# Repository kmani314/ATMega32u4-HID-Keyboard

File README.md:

## ATMega32u4 HID Keyboard
###### Board Project 2019 - Krishna Mani
This is software for ATMega32u4 or compatible AVR hardware USB chips that implements a standard-complying HID keyboard using only AVR-LIBC.

I used these for reference when coding:

1. https://www.avrfreaks.net/forum/usb-initialization-problem
2. https://www.pjrc.com/teensy/usb_keyboard.html
3. https://www.usb.org/sites/default/files/documents/hid1_11.pdf
4. https://www.avrfreaks.net/forum/help-properly-initializing-usb-hardware-atmega32u4
5. https://www.beyondlogic.org/usbnutshell/usb1.shtml
6. http://ww1.microchip.com/downloads/en/devicedoc/atmel-7766-8-bit-avr-atmega16u4-32u4_datasheet.pdf
7. https://github.com/arduino/ArduinoCore-avr/blob/master/cores/arduino/USBCore.cpp
8. http://sdphca.ucsd.edu/lab_equip_manuals/usb_20.pdf

Finished Board:

### Hardware

##### Microcontroller
The ATMega32u4 controls the scanning matrix and the USB interface. I chose it because of its hardware USB interface and because it has enough I/O pins to support the whole keyboard without needing any multiplexing. It also has enough flash and SRAM for storing layouts. The 32u4 on the keyboard runs at 16mHz from an external crystal oscillator with 22pF load capacitors. It is powered directly from the USB lines with filtering capacitors.
##### PCBs
Initially, I needed to test the main microcontroller circuit of the keyboard to ensure that it worked and that the USB worked, because I had developed on an Arduino Leonardo. (boards/ATMegaTestingBoard.brd)

##### ATMega32u4 Circuit
The portion of the board for the ATMega32u4 is fairly standard for this chip and is similar to the Arduino Leonardo, excluding the power regulators. It consists of the chip, the oscillator and load caps, the power and layer leds, the reset switch, the USB connector and data resistors, the ICSP pins, and the filtering caps on the underside of the board.

Top / Bottom (boards/Keyboard.brd):

The rest of the board is the scanning matrix. The rows and columns use up the majority of the I/O on the chip.
The matrix is standard for a keyboard - one pin of each switch in a column is connected through a diode to every other one in the column. Then, the remaining pin in each switch is common with the row. I used through hole diodes because they are much easier to solder. The switches are standard mechanical keyboard switches, and the footprints are from here: https://github.com/mknyszek/gateron-eagle
To read the matrix, the row pins are pulled high through internal pull-up resistors. One column at a time is set low, so that a pressed key would pull the row pin low, signaling a key press at the current row and column index.

Top / Bottom matrix (boards/Keyboard.brd):

##### Board Assembly
Assembling the board was straightforward except for the SMD components, specifically the TQFP ATMega32u4. It is really easy to bridge several pads very quickly, and completely ruin the chip. I soldered these by holding them in place and tacking down the corners so the chip didn’t move. I used a lot of flux, then with very little solder dragged the iron across the pins. The USB connector is also really difficult, I soldered the anchor pins and then the pins. It is really easy to bridge the pins with the ground enclosure. Using super glue after ensures that the connector doesn’t snap off when you unplug the cable.

### Code
##### USB
First, the USB controller of the 32u4 is initialized. This is handled in the function `usb_init()`. The PLL (Phase Locked Loop) is initialized, taking the external clock as input. It runs at 48mHz and acts as the USB clock. After the USB controller is initialized, the control endpoint is set up and will receive setup packets from the host. The setup packets, handled in the ISR `USB_gen_vect`, elicit responses from the keyboard based on the values of bmRequestType and bRequest, which determine the type of request. After the host has requested and received the USB descriptors, and the keyboard has correctly responded to HID-specific requests, the host can enumerate the device and use it as an input device.

The key repeat feature of modern keyboards is handled separately from the standard functions `usb_send()` and `usb_send_keypress()`. If a key is held down for some period of time, it should be repeated until it is released. This is taken care of in the ISR `USB_gen_vect`, specifically when the SOFE (start of frame) bit is set. This interrupt triggers at 1kHz, which is how often the host sends start of frame packets. If no keypresses have been generated since the period time, which is kept track of with keyboard_idle_value and current_idle, the entire HID report is resent to facilitate key repeat. The period of time the device should wait before resending the report is set from the wValue in the HID request SET_IDLE.
##### Matrix Software
The scanning matrix of the keyboard uses the current sourcing and internal pullups of the I/O ports on the 32u4. Because of the orientation of the diodes, the columns of the keyboard are set low when they are going to be read. The rows are always pulled up, meaning that if a key is pressed, it will be pulled low because the switch is connecting the row and columns. The matrix scanning is repeated quickly, and changes in key state are recorded in the six-byte USB HID report. The report is six bytes to support six concurrent key presses. The keyboard dynamically assigns and removes keys from the report to support 6-key-rollover, and it also resets the reports on layout layer shifts to prevent strange glitches. The meta and special keys like CTRL, ALT, and SHIFT have their own byte apart from the report, where each bit represents a different key. This is according to the USB HID Spec.

The rows and columns of the recorded keypresses are translated into actual keycodes from the specified layout in `layout.h`. The layout is written from the standard HID keycodes in `keys.h`. Because the keyboard does not have enough physical keys to support all the letters, function, and number keys, some keys are macros that change the mappings of all the keys. These keys are handled separately and do not generate keypress events on their own. Rather, they update the current layer that the scanning matrix is reporting keypresses from to change the keycodes.
### Improvements
1. Changing the routing on PORTD to make it iterable, making the code more readable and cleaner.
2. Using USB-C instead of micro b, meaning that you would not need a dongle for use with newer macs. This would, however, make it much more difficult to solder and the PCB more complicated, since the USB-C connectors have 24 pins.
3. Using the BGA package for the ATMega32u4 so that it could fit in between switches on the underside of the board, meaning that the PCB would only have to be as big as to fit the switches. This would make it more compact.
4. Using symmetrical keycaps so that the keycaps aren’t skewed when using keyboard layouts other than QWERTY.
5. Adding support for a dedicated FN key endpoint and Caps lock and num lock; currently you have to remap function to media keys with a third party tool for the media keys on the keyboard to work on touch bar macs.
6. Move the ICSP connector down, right now you have to bend the power LED up for the connector to make contact with the headers.
7. Route the third layer led to a different I/O port, right now only two of the three LEDs work.

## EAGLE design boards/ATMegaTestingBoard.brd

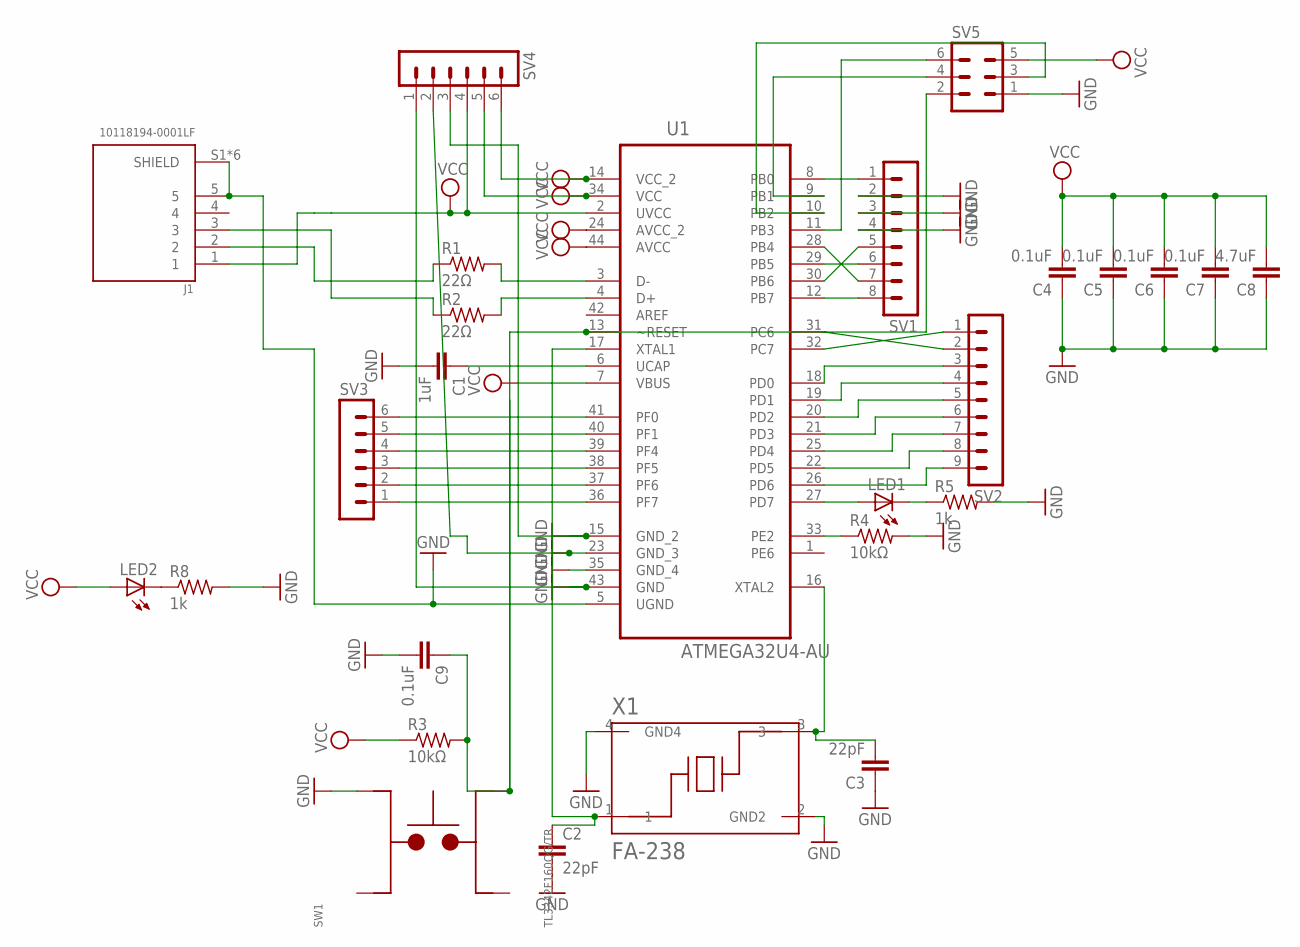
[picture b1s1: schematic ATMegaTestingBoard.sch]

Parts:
C1: 1uF; C0805
C2, C3: 22pF; C0805
C4, C5, C6, C7, C9: 0.1uF; C0805
C8: 4.7uF; C0805
J1: 10118194-0001LF; AMPHENOL_10118194-0001LF
LED1, LED2: LEDCHIPLED_0805; CHIPLED_0805
R1, R2: 22Ω; R0805
R3, R4: 10kΩ; R0805
R5, R8: 1k; R0805
SV1: MA08-1
SV2: MA09-1
SV3, SV4: MA06-1
SV5: MA03-2
SW1: TL3342F160QG/TR; SW_TL3342F160QG/TR
U1: ATMEGA32U4-AU; QFP80P1200X1200X120-44N
X1: FA-238; OSCCC320X250X70-4N

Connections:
GND: C1.2, C2.2, C3.1, C4.1, C5.1, C6.1, C7.1, C8.1, C9.2, J1.5, J1.S1 (SHIELD), J1.S2 (SHIELD), J1.S3 (SHIELD), J1.S4 (SHIELD), J1.S5 (SHIELD), J1.S6 (SHIELD), R4.2, R5.2, R8.2, SV1.2, SV1.3, SV1.4, SV4.1, SV4.2, SV4.3, SV5.1, SW1.4, U1.5 (UGND), U1.15 (GND_2), U1.23 (GND_3), U1.35 (GND_4), U1.43 (GND), X1.2 (GND2), X1.4 (GND4)
unnamed: R1.2, U1.3 (D-)
unnamed: J1.3, R2.1
unnamed: J1.2, R1.1
unnamed: C1.1, U1.6 (UCAP)
unnamed: R2.2, U1.4 (D+)
unnamed: SV1.1, U1.8 (PB0)
unnamed: C9.1, R3.2, SV5.2, SW1.2, U1.13 (~RESET)
unnamed: C2.1, U1.17 (XTAL1), X1.1
unnamed: R4.1, U1.33 (PE2)
unnamed: C3.2, U1.16 (XTAL2), X1.3
unnamed: LED1.A, U1.27 (PD7)
unnamed: LED1.C, R5.1
unnamed: SV1.7, U1.28 (PB4)
unnamed: SV1.5, U1.30 (PB6)
unnamed: LED2.C, R8.1
unnamed: SV5.6, U1.11 (PB3)
unnamed: SV5.4, U1.9 (PB1)
unnamed: SV5.3, U1.10 (PB2)
unnamed: SV1.6, U1.29 (PB5)
unnamed: SV2.2, U1.31 (PC6)
unnamed: SV2.1, U1.32 (PC7)
unnamed: SV1.8, U1.12 (PB7)
unnamed: SV2.3, U1.18 (PD0)
unnamed: SV2.4, U1.19 (PD1)
unnamed: SV2.5, U1.20 (PD2)
unnamed: SV2.6, U1.21 (PD3)
unnamed: SV2.7, U1.25 (PD4)
unnamed: SV2.8, U1.22 (PD5)
unnamed: SV2.9, U1.26 (PD6)
unnamed: SV3.6, U1.41 (PF0)
unnamed: SV3.5, U1.40 (PF1)
unnamed: SV3.4, U1.39 (PF4)
unnamed: SV3.3, U1.38 (PF5)
unnamed: SV3.2, U1.37 (PF6)
unnamed: SV3.1, U1.36 (PF7)
VCC: C4.2, C5.2, C6.2, C7.2, C8.2, J1.1, LED2.A, R3.1, SV4.4, SV4.5, SV4.6, SV5.5, U1.2 (UVCC), U1.7 (VBUS), U1.14 (VCC_2), U1.24 (AVCC_2), U1.34 (VCC), U1.44 (AVCC)

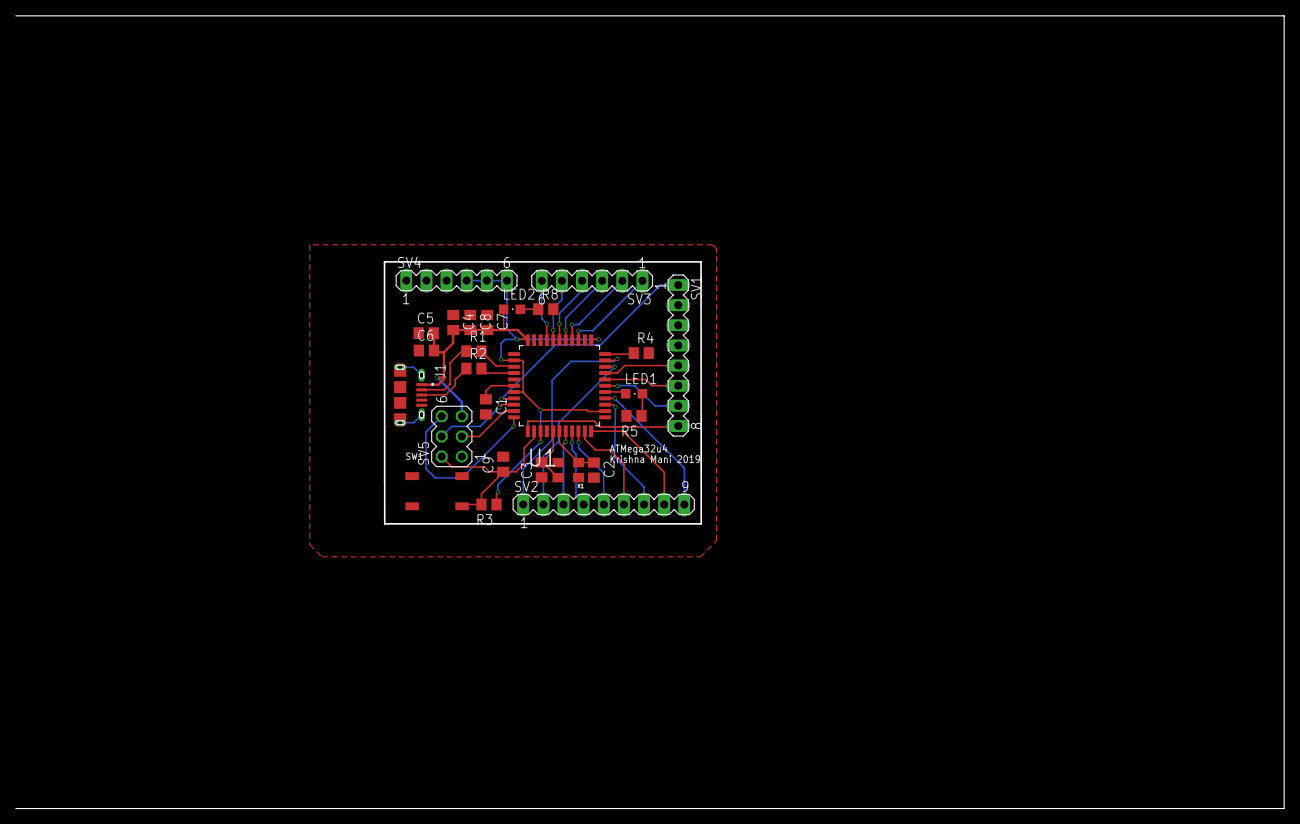
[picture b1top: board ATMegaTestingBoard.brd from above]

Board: 2 copper layers, 160.0 x 100.0 mm, 26 parts (0 on the bottom side), 37 nets.

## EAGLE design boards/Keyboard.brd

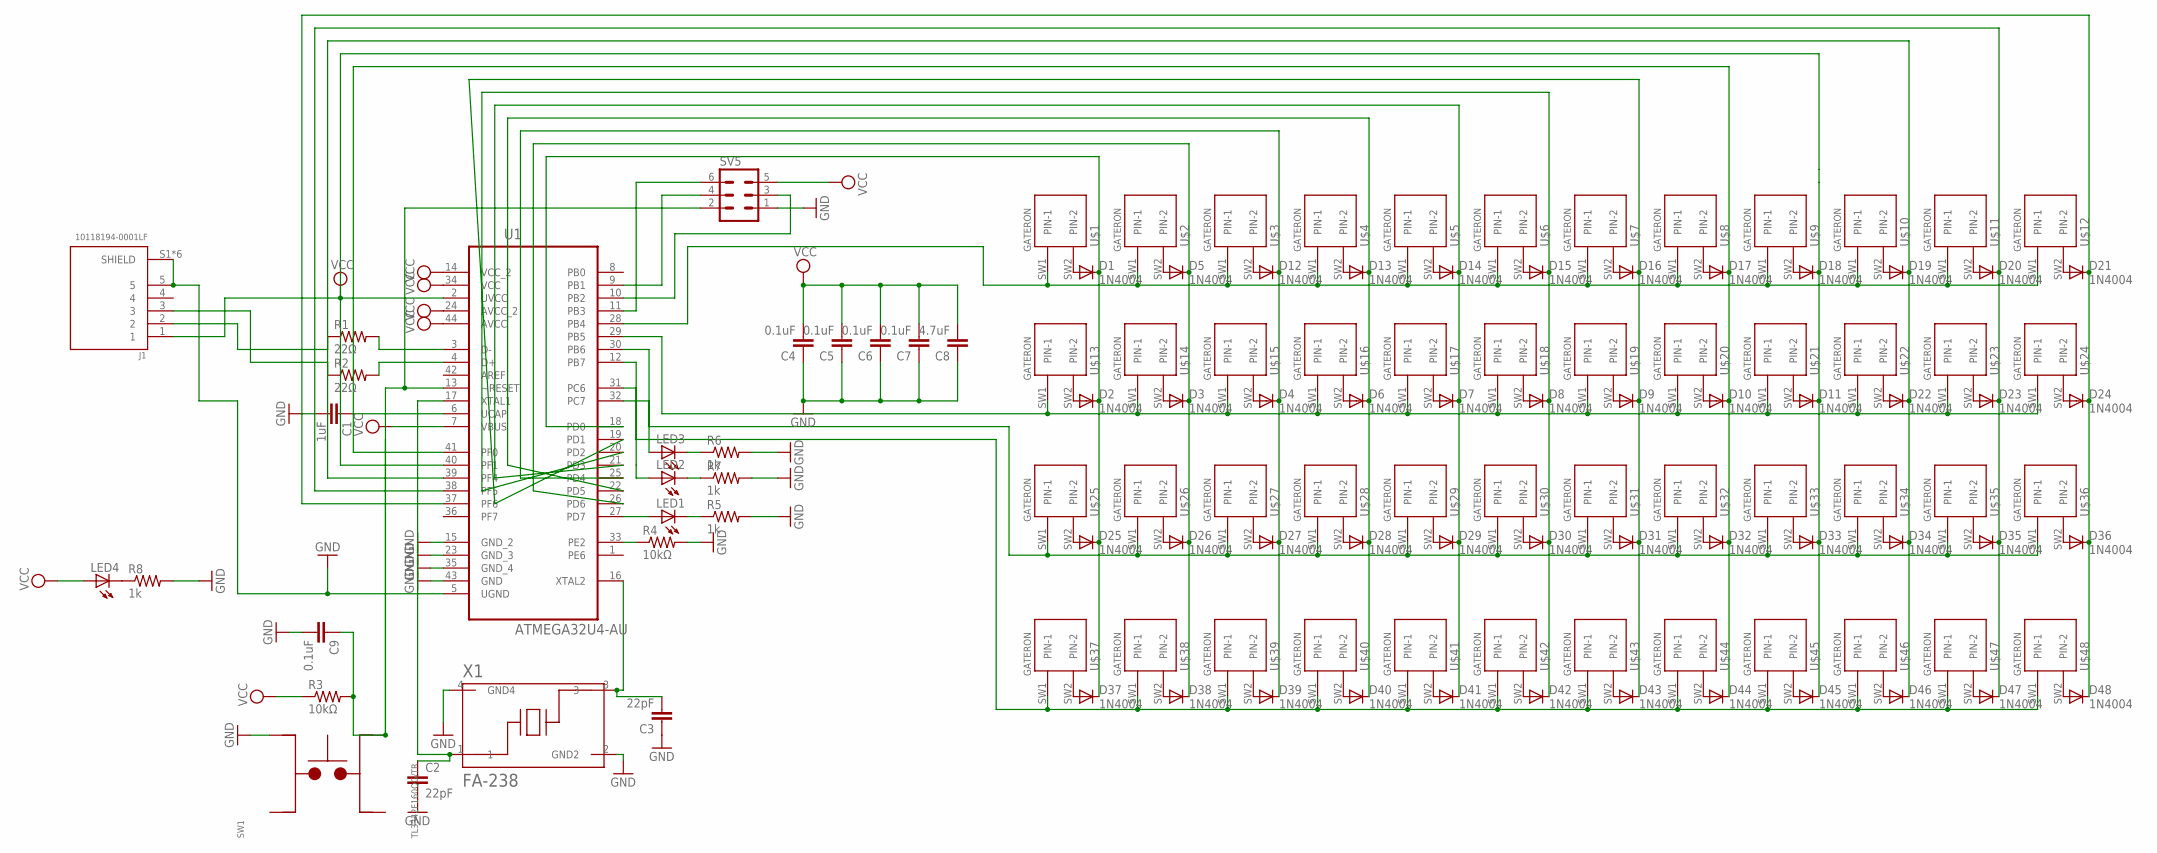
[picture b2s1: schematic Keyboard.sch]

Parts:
C1: 1uF; C0805
C2, C3: 22pF; C0805
C4, C5, C6, C7, C9: 0.1uF; C0805
C8: 4.7uF; C0805
D1, D2, D3, D4, D5, D6, D7, D8, D9, D10, D11, D12, D13, D14, D15, D16, D17, D18, D19, D20, D21, D22, D23, D24, D25, D26, D27, D28, D29, D30, D31, D32, D33, D34, D35, D36, D37, D38, D39, D40, D41, D42, D43, D44, D45, D46, D47, D48: 1N4004; DO41-10
J1: 10118194-0001LF; AMPHENOL_10118194-0001LF
LED1, LED2, LED3, LED4: LED_ELD260; LED_LD260
R1, R2: 22Ω; R0805
R3, R4: 10kΩ; R0805
R5, R6, R7, R8: 1k; R0805
SV5: MA03-2
SW1: TL3342F160QG/TR; SW_TL3342F160QG/TR
U1: ATMEGA32U4-AU; QFP80P1200X1200X120-44N
U$1, U$2, U$3, U$4, U$5, U$6, U$7, U$8, U$9, U$10, U$11, U$12, U$13, U$14, U$15, U$16, U$17, U$18, U$19, U$20, U$21, U$22, U$23, U$24, U$25, U$26, U$27, U$28, U$29, U$30, U$31, U$32, U$33, U$34, U$35, U$36, U$37, U$38, U$39, U$40, U$41, U$42, U$43, U$44, U$45, U$46, U$47, U$48: GATERON
X1: FA-238; OSCCC320X250X70-4N

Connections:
GND: C1.2, C2.2, C3.1, C4.1, C5.1, C6.1, C7.1, C8.1, C9.2, J1.5, J1.S1 (SHIELD), J1.S2 (SHIELD), J1.S3 (SHIELD), J1.S4 (SHIELD), J1.S5 (SHIELD), J1.S6 (SHIELD), R4.2, R5.2, R6.2, R7.2, R8.2, SV5.1, SW1.4, U1.5 (UGND), U1.15 (GND_2), U1.23 (GND_3), U1.35 (GND_4), U1.43 (GND), X1.2 (GND2), X1.4 (GND4)
unnamed: R1.2, U1.3 (D-)
unnamed: J1.3, R2.1
unnamed: J1.2, R1.1
unnamed: C1.1, U1.6 (UCAP)
unnamed: R2.2, U1.4 (D+)
unnamed: U1.28 (PB4), U$1.SW1 (PIN-1), U$2.SW1 (PIN-1), U$3.SW1 (PIN-1), U$4.SW1 (PIN-1), U$5.SW1 (PIN-1), U$6.SW1 (PIN-1), U$7.SW1 (PIN-1), U$8.SW1 (PIN-1), U$9.SW1 (PIN-1), U$10.SW1 (PIN-1), U$11.SW1 (PIN-1), U$12.SW1 (PIN-1)
unnamed: C9.1, R3.2, SV5.2, SW1.2, U1.13 (~RESET)
unnamed: C2.1, U1.17 (XTAL1), X1.1
unnamed: R4.1, U1.33 (PE2)
unnamed: C3.2, U1.16 (XTAL2), X1.3
unnamed: LED1.A, U1.27 (PD7)
unnamed: LED1.K (C), R5.1
unnamed: U1.29 (PB5), U$13.SW1 (PIN-1), U$14.SW1 (PIN-1), U$15.SW1 (PIN-1), U$16.SW1 (PIN-1), U$17.SW1 (PIN-1), U$18.SW1 (PIN-1), U$19.SW1 (PIN-1), U$20.SW1 (PIN-1), U$21.SW1 (PIN-1), U$22.SW1 (PIN-1), U$23.SW1 (PIN-1), U$24.SW1 (PIN-1)
unnamed: D2.A, U$13.SW2 (PIN-2)
unnamed: LED4.K (C), R8.1
unnamed: SV5.6, U1.11 (PB3)
unnamed: SV5.4, U1.9 (PB1)
unnamed: SV5.3, U1.10 (PB2)
unnamed: D3.A, U$14.SW2 (PIN-2)
unnamed: D1.A, U$1.SW2 (PIN-2)
unnamed: D4.A, U$15.SW2 (PIN-2)
unnamed: D6.A, U$16.SW2 (PIN-2)
unnamed: D7.A, U$17.SW2 (PIN-2)
unnamed: D5.A, U$2.SW2 (PIN-2)
unnamed: D8.A, U$18.SW2 (PIN-2)
unnamed: D9.A, U$19.SW2 (PIN-2)
unnamed: D10.A, U$20.SW2 (PIN-2)
unnamed: D11.A, U$21.SW2 (PIN-2)
unnamed: D22.A, U$22.SW2 (PIN-2)
unnamed: D23.A, U$23.SW2 (PIN-2)
unnamed: D12.A, U$3.SW2 (PIN-2)
unnamed: D13.A, U$4.SW2 (PIN-2)
unnamed: D14.A, U$5.SW2 (PIN-2)
unnamed: D15.A, U$6.SW2 (PIN-2)
unnamed: D16.A, U$7.SW2 (PIN-2)
unnamed: D17.A, U$8.SW2 (PIN-2)
unnamed: D18.A, U$9.SW2 (PIN-2)
unnamed: D19.A, U$10.SW2 (PIN-2)
unnamed: D20.A, U$11.SW2 (PIN-2)
unnamed: D21.A, U$12.SW2 (PIN-2)
unnamed: D24.A, U$24.SW2 (PIN-2)
unnamed: U1.30 (PB6), U$25.SW1 (PIN-1), U$26.SW1 (PIN-1), U$27.SW1 (PIN-1), U$28.SW1 (PIN-1), U$29.SW1 (PIN-1), U$30.SW1 (PIN-1), U$31.SW1 (PIN-1), U$32.SW1 (PIN-1), U$33.SW1 (PIN-1), U$34.SW1 (PIN-1), U$35.SW1 (PIN-1), U$36.SW1 (PIN-1)
unnamed: D25.A, U$25.SW2 (PIN-2)
unnamed: D26.A, U$26.SW2 (PIN-2)
unnamed: D27.A, U$27.SW2 (PIN-2)
unnamed: D28.A, U$28.SW2 (PIN-2)
unnamed: D29.A, U$29.SW2 (PIN-2)
unnamed: D30.A, U$30.SW2 (PIN-2)
unnamed: D31.A, U$31.SW2 (PIN-2)
unnamed: D32.A, U$32.SW2 (PIN-2)
unnamed: D33.A, U$33.SW2 (PIN-2)
unnamed: D34.A, U$34.SW2 (PIN-2)
unnamed: D35.A, U$35.SW2 (PIN-2)
unnamed: D36.A, U$36.SW2 (PIN-2)
unnamed: U1.12 (PB7), U$37.SW1 (PIN-1), U$38.SW1 (PIN-1), U$39.SW1 (PIN-1), U$40.SW1 (PIN-1), U$41.SW1 (PIN-1), U$42.SW1 (PIN-1), U$43.SW1 (PIN-1), U$44.SW1 (PIN-1), U$45.SW1 (PIN-1), U$46.SW1 (PIN-1), U$47.SW1 (PIN-1), U$48.SW1 (PIN-1)
unnamed: D37.A, U$37.SW2 (PIN-2)
unnamed: D38.A, U$38.SW2 (PIN-2)
unnamed: D39.A, U$39.SW2 (PIN-2)
unnamed: D40.A, U$40.SW2 (PIN-2)
unnamed: D41.A, U$41.SW2 (PIN-2)
unnamed: D42.A, U$42.SW2 (PIN-2)
unnamed: D43.A, U$43.SW2 (PIN-2)
unnamed: D44.A, U$44.SW2 (PIN-2)
unnamed: D45.A, U$45.SW2 (PIN-2)
unnamed: D46.A, U$46.SW2 (PIN-2)
unnamed: D47.A, U$47.SW2 (PIN-2)
unnamed: D48.A, U$48.SW2 (PIN-2)
unnamed: D1.C, D2.C, D25.C, D37.C, U1.18 (PD0)
unnamed: D3.C, D5.C, D26.C, D38.C, U1.26 (PD6)
unnamed: D4.C, D12.C, D27.C, D39.C, U1.25 (PD4)
unnamed: D6.C, D13.C, D28.C, D40.C, U1.22 (PD5)
unnamed: D7.C, D14.C, D29.C, D41.C, U1.21 (PD3)
unnamed: D8.C, D15.C, D30.C, D42.C, U1.20 (PD2)
unnamed: D9.C, D16.C, D31.C, D43.C, U1.19 (PD1)
unnamed: D10.C, D17.C, D32.C, D44.C, U1.41 (PF0)
unnamed: D11.C, D18.C, D33.C, D45.C, U1.40 (PF1)
unnamed: D19.C, D22.C, D34.C, D46.C, U1.39 (PF4)
unnamed: D20.C, D23.C, D35.C, D47.C, U1.38 (PF5)
unnamed: D21.C, D24.C, D36.C, D48.C, U1.37 (PF6)
unnamed: LED3.K (C), R6.1
unnamed: LED2.K (C), R7.1
unnamed: LED2.A, U1.31 (PC6)
unnamed: LED3.A, U1.32 (PC7)
VCC: C4.2, C5.2, C6.2, C7.2, C8.2, J1.1, LED4.A, R3.1, SV5.5, U1.2 (UVCC), U1.7 (VBUS), U1.14 (VCC_2), U1.24 (AVCC_2), U1.34 (VCC), U1.44 (AVCC)

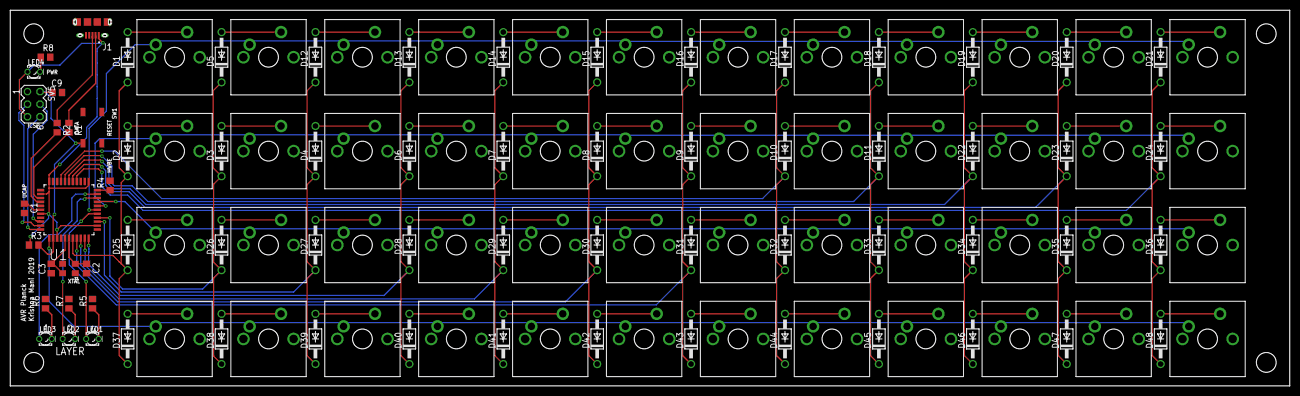
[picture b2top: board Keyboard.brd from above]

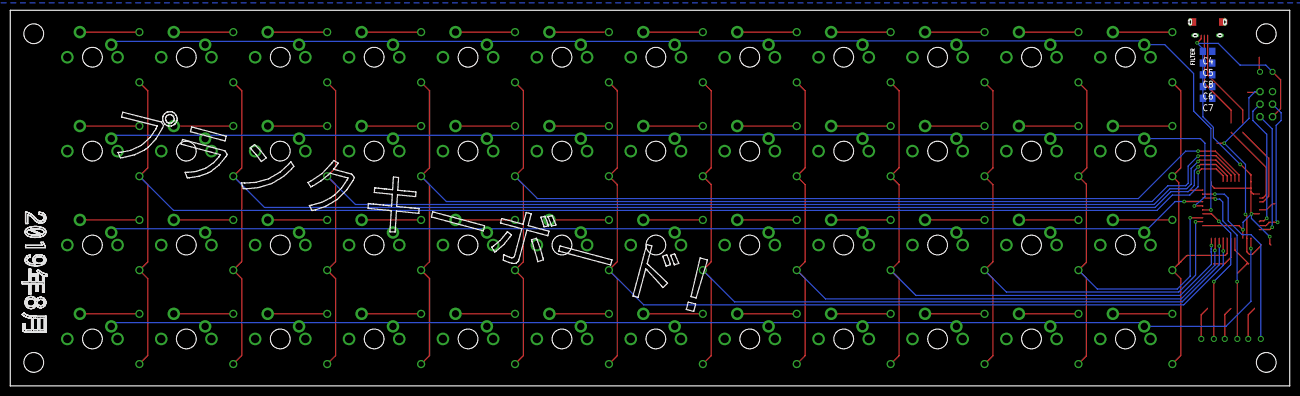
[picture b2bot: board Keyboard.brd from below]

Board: 2 copper layers, 258.9 x 76.0 mm, 122 parts (5 on the bottom side), 85 nets.

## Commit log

2019-07-15 Add basic readme
2019-07-16 Basic CMake, usb_init
2019-07-17 Recongnizes EORSTE now
2019-07-18 Not really working
2019-07-18 Works, receiving RXSTPI, problem was bad PLL setup
2019-07-19 Add README references, usb_config_status bool
2019-07-19 README
2019-07-19 github markdown is strange
2019-07-19 almost fixed readme
2019-07-19 add ul to readme
2019-07-19 alright, finally add ul
2019-07-19 Update README for first part of writeup
2019-07-19 Add README table
2019-07-19 fix table
2019-07-19 final table
2019-07-21 Started on setup packets and descriptors
2019-07-22 Working on descriptors
2019-07-23 Write HID descriptor
2019-07-23 Finish Descriptors
2019-07-24 address setup done, receives GET_DESCRIPTOR
2019-07-26 Add working device enumeration
2019-07-26 working enumeration with 32 byte endpoint properly setup
2019-07-26 Working Device, Configuration, Interface, Endpoint Enumeration. Need to work on HID class-specific request handling
2019-07-27 Add HID requests, still have to do SOFE idle checking
2019-07-27 Basic keypresses work, need to fix key repeat. Problem was GET_STATUS condition had = instead of ==, didn't notice for 6 hours
2019-07-29 Add full ASCII, fix repeat glitch, add keys.h, fix timeout issue
2019-08-12 Matrix isn't working, but sorta is
2019-08-12 matrix works, need to do debounce, layer shift, key state tracking
2019-08-13 Almost working
2019-08-14 Works fully, still some minor glitches to fix
2019-08-14 0.1 Finished, I haven't found anything that's broken yet
2019-08-14 fixed some glitches, works better now
2019-08-14 Add post build script to cmake, add interval usb throttling to fix os rejection, changed my layout
2019-08-17 fixed random key glitch bug, change my layout. fully working now
2019-08-17 Update Vendor IDs
2019-08-17 Work on writeup, add board files
2019-08-19 D V O R A K
2019-08-24 Add img/, writeup is done
2019-08-24 fix readme
2019-08-24 fix images and headings in readme
2019-08-24 newlines in readme
2019-08-24 fix return types for matrix functions
2019-08-24 Add improvements section to readme
2022-12-18 Fix #2
2022-12-19 clarify a comment
2022-12-19 fix the fix
2023-01-21 add building via gcc makefile
